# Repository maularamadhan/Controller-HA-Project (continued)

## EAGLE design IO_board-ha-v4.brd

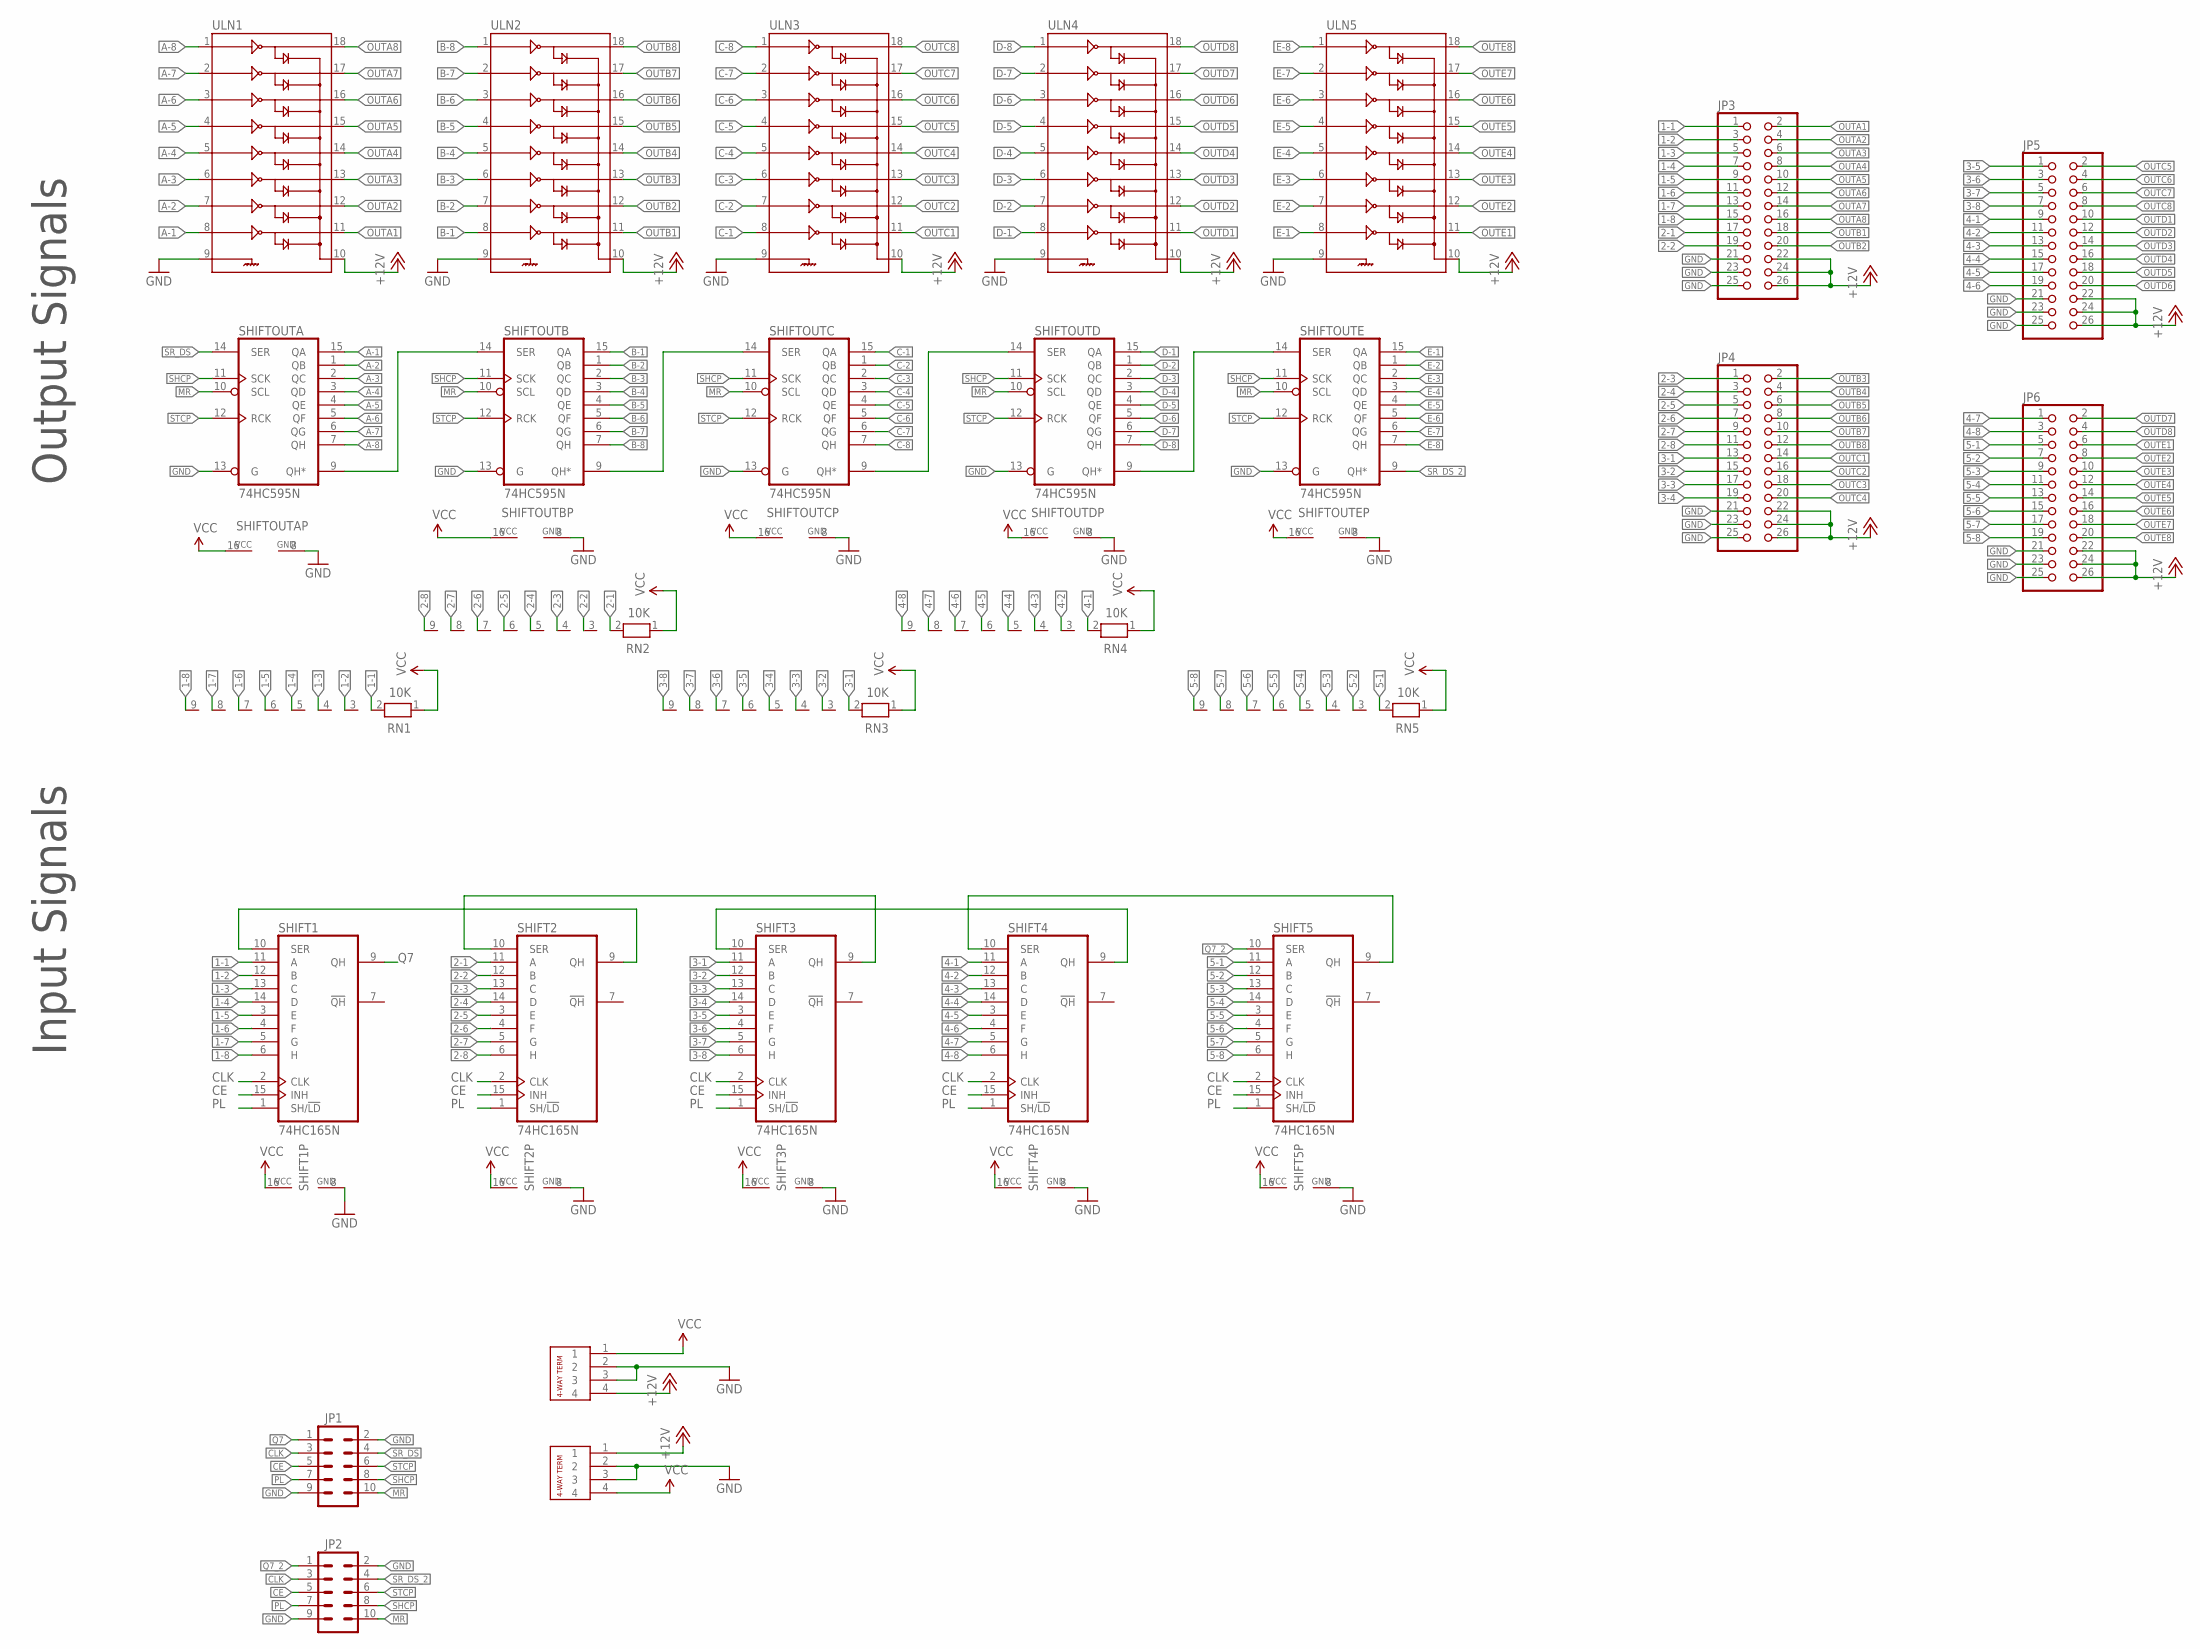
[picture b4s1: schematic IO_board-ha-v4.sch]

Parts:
J1, J2: 4-PIN-CON-1759017
JP1, JP2: M05X2SHD; 2X5-SHROUDED
JP3, JP4, JP5, JP6: PINHD-2X13; 2X13
RN1, RN2, RN3, RN4, RN5: 10K; RN-9
SHIFT1, SHIFT2, SHIFT3, SHIFT4, SHIFT5: 74HC165N; DIL16
SHIFTOUTA: 74HC595N; DIL16
SHIFTOUTB: 74HC595N; DIL16
SHIFTOUTC: 74HC595N; DIL16
SHIFTOUTD: 74HC595N; DIL16
SHIFTOUTE: 74HC595N; DIL16
ULN1, ULN2, ULN3, ULN4, ULN5: ULN2803DIP; DIL18

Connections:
1-1: JP3.1, RN1.2, SHIFT1.11 (A)
1-2: JP3.3, RN1.3, SHIFT1.12 (B)
1-3: JP3.5, RN1.4, SHIFT1.13 (C)
1-4: JP3.7, RN1.5, SHIFT1.14 (D)
1-5: JP3.9, RN1.6, SHIFT1.3 (E)
1-6: JP3.11, RN1.7, SHIFT1.4 (F)
1-7: JP3.13, RN1.8, SHIFT1.5 (G)
1-8: JP3.15, RN1.9, SHIFT1.6 (H)
2-1: JP3.17, RN2.2, SHIFT2.11 (A)
2-2: JP3.19, RN2.3, SHIFT2.12 (B)
2-3: JP4.1, RN2.4, SHIFT2.13 (C)
2-4: JP4.3, RN2.5, SHIFT2.14 (D)
2-5: JP4.5, RN2.6, SHIFT2.3 (E)
2-6: JP4.7, RN2.7, SHIFT2.4 (F)
2-7: JP4.9, RN2.8, SHIFT2.5 (G)
2-8: JP4.11, RN2.9, SHIFT2.6 (H)
3-1: JP4.13, RN3.2, SHIFT3.11 (A)
3-2: JP4.15, RN3.3, SHIFT3.12 (B)
3-3: JP4.17, RN3.4, SHIFT3.13 (C)
3-4: JP4.19, RN3.5, SHIFT3.14 (D)
3-5: JP5.1, RN3.6, SHIFT3.3 (E)
3-6: JP5.3, RN3.7, SHIFT3.4 (F)
3-7: JP5.5, RN3.8, SHIFT3.5 (G)
3-8: JP5.7, RN3.9, SHIFT3.6 (H)
4-1: JP5.9, RN4.2, SHIFT4.11 (A)
4-2: JP5.11, RN4.3, SHIFT4.12 (B)
4-3: JP5.13, RN4.4, SHIFT4.13 (C)
4-4: JP5.15, RN4.5, SHIFT4.14 (D)
4-5: JP5.17, RN4.6, SHIFT4.3 (E)
4-6: JP5.19, RN4.7, SHIFT4.4 (F)
4-7: JP6.1, RN4.8, SHIFT4.5 (G)
4-8: JP6.3, RN4.9, SHIFT4.6 (H)
5-1: JP6.5, RN5.2, SHIFT5.11 (A)
5-2: JP6.7, RN5.3, SHIFT5.12 (B)
5-3: JP6.9, RN5.4, SHIFT5.13 (C)
5-4: JP6.11, RN5.5, SHIFT5.14 (D)
5-5: JP6.13, RN5.6, SHIFT5.3 (E)
5-6: JP6.15, RN5.7, SHIFT5.4 (F)
5-7: JP6.17, RN5.8, SHIFT5.5 (G)
5-8: JP6.19, RN5.9, SHIFT5.6 (H)
+12V: J1.4, J2.1, JP3.22, JP3.24, JP3.26, JP4.22, JP4.24, JP4.26, JP5.22, JP5.24, JP5.26, JP6.22, JP6.24, JP6.26, ULN1.10, ULN2.10, ULN3.10, ULN4.10, ULN5.10
A-1: SHIFTOUTA.15 (QA), ULN1.8
A-2: SHIFTOUTA.1 (QB), ULN1.7
A-3: SHIFTOUTA.2 (QC), ULN1.6
A-4: SHIFTOUTA.3 (QD), ULN1.5
A-5: SHIFTOUTA.4 (QE), ULN1.4
A-6: SHIFTOUTA.5 (QF), ULN1.3
A-7: SHIFTOUTA.6 (QG), ULN1.2
A-8: SHIFTOUTA.7 (QH), ULN1.1
B-1: SHIFTOUTB.15 (QA), ULN2.8
B-2: SHIFTOUTB.1 (QB), ULN2.7
B-3: SHIFTOUTB.2 (QC), ULN2.6
B-4: SHIFTOUTB.3 (QD), ULN2.5
B-5: SHIFTOUTB.4 (QE), ULN2.4
B-6: SHIFTOUTB.5 (QF), ULN2.3
B-7: SHIFTOUTB.6 (QG), ULN2.2
B-8: SHIFTOUTB.7 (QH), ULN2.1
C-1: SHIFTOUTC.15 (QA), ULN3.8
C-2: SHIFTOUTC.1 (QB), ULN3.7
C-3: SHIFTOUTC.2 (QC), ULN3.6
C-4: SHIFTOUTC.3 (QD), ULN3.5
C-5: SHIFTOUTC.4 (QE), ULN3.4
C-6: SHIFTOUTC.5 (QF), ULN3.3
C-7: SHIFTOUTC.6 (QG), ULN3.2
C-8: SHIFTOUTC.7 (QH), ULN3.1
CE: JP1.5, JP2.5, SHIFT1.15 (INH), SHIFT2.15 (INH), SHIFT3.15 (INH), SHIFT4.15 (INH), SHIFT5.15 (INH)
CLK: JP1.3, JP2.3, SHIFT1.2 (CLK), SHIFT2.2 (CLK), SHIFT3.2 (CLK), SHIFT4.2 (CLK), SHIFT5.2 (CLK)
D-1: SHIFTOUTD.15 (QA), ULN4.8
D-2: SHIFTOUTD.1 (QB), ULN4.7
D-3: SHIFTOUTD.2 (QC), ULN4.6
D-4: SHIFTOUTD.3 (QD), ULN4.5
D-5: SHIFTOUTD.4 (QE), ULN4.4
D-6: SHIFTOUTD.5 (QF), ULN4.3
D-7: SHIFTOUTD.6 (QG), ULN4.2
D-8: SHIFTOUTD.7 (QH), ULN4.1
E-1: SHIFTOUTE.15 (QA), ULN5.8
E-2: SHIFTOUTE.1 (QB), ULN5.7
E-3: SHIFTOUTE.2 (QC), ULN5.6
E-4: SHIFTOUTE.3 (QD), ULN5.5
E-5: SHIFTOUTE.4 (QE), ULN5.4
E-6: SHIFTOUTE.5 (QF), ULN5.3
E-7: SHIFTOUTE.6 (QG), ULN5.2
E-8: SHIFTOUTE.7 (QH), ULN5.1
GND: J1.2, J1.3, J2.2, J2.3, JP1.2, JP1.9, JP2.2, JP2.9, JP3.21, JP3.23, JP3.25, JP4.21, JP4.23, JP4.25, JP5.21, JP5.23, JP5.25, JP6.21, JP6.23, JP6.25, SHIFT1.8 (GND), SHIFT2.8 (GND), SHIFT3.8 (GND), SHIFT4.8 (GND), SHIFT5.8 (GND), SHIFTOUTA.8 (GND), SHIFTOUTA.13 (G), SHIFTOUTB.8 (GND), SHIFTOUTB.13 (G), SHIFTOUTC.8 (GND), SHIFTOUTC.13 (G), SHIFTOUTD.8 (GND), SHIFTOUTD.13 (G), SHIFTOUTE.8 (GND), SHIFTOUTE.13 (G), ULN1.9, ULN2.9, ULN3.9, ULN4.9, ULN5.9
MR: JP1.10, JP2.10, SHIFTOUTA.10 (SCL), SHIFTOUTB.10 (SCL), SHIFTOUTC.10 (SCL), SHIFTOUTD.10 (SCL), SHIFTOUTE.10 (SCL)
unnamed: SHIFT2.10 (SER), SHIFT3.9 (QH)
unnamed: SHIFT3.10 (SER), SHIFT4.9 (QH)
unnamed: SHIFT4.10 (SER), SHIFT5.9 (QH)
unnamed: SHIFTOUTA.9 (QH*), SHIFTOUTB.14 (SER)
unnamed: SHIFTOUTC.9 (QH*), SHIFTOUTD.14 (SER)
unnamed: SHIFTOUTB.9 (QH*), SHIFTOUTC.14 (SER)
unnamed: SHIFTOUTD.9 (QH*), SHIFTOUTE.14 (SER)
unnamed: SHIFT1.10 (SER), SHIFT2.9 (QH)
OUTA1: JP3.2, ULN1.11
OUTA2: JP3.4, ULN1.12
OUTA3: JP3.6, ULN1.13
OUTA4: JP3.8, ULN1.14
OUTA5: JP3.10, ULN1.15
OUTA6: JP3.12, ULN1.16
OUTA7: JP3.14, ULN1.17
OUTA8: JP3.16, ULN1.18
OUTB1: JP3.18, ULN2.11
OUTB2: JP3.20, ULN2.12
OUTB3: JP4.2, ULN2.13
OUTB4: JP4.4, ULN2.14
OUTB5: JP4.6, ULN2.15
OUTB6: JP4.8, ULN2.16
OUTB7: JP4.10, ULN2.17
OUTB8: JP4.12, ULN2.18
OUTC1: JP4.14, ULN3.11
OUTC2: JP4.16, ULN3.12
OUTC3: JP4.18, ULN3.13
OUTC4: JP4.20, ULN3.14
OUTC5: JP5.2, ULN3.15
OUTC6: JP5.4, ULN3.16
OUTC7: JP5.6, ULN3.17
OUTC8: JP5.8, ULN3.18
OUTD1: JP5.10, ULN4.11
OUTD2: JP5.12, ULN4.12
OUTD3: JP5.14, ULN4.13
OUTD4: JP5.16, ULN4.14
OUTD5: JP5.18, ULN4.15
OUTD6: JP5.20, ULN4.16
OUTD7: JP6.2, ULN4.17
OUTD8: JP6.4, ULN4.18
OUTE1: JP6.6, ULN5.11
OUTE2: JP6.8, ULN5.12
OUTE3: JP6.10, ULN5.13
OUTE4: JP6.12, ULN5.14
OUTE5: JP6.14, ULN5.15
OUTE6: JP6.16, ULN5.16
OUTE7: JP6.18, ULN5.17
OUTE8: JP6.20, ULN5.18
PL: JP1.7, JP2.7, SHIFT1.1 (SH/!LD), SHIFT2.1 (SH/!LD), SHIFT3.1 (SH/!LD), SHIFT4.1 (SH/!LD), SHIFT5.1 (SH/!LD)
Q7: JP1.1, SHIFT1.9 (QH)
Q7_2: JP2.1, SHIFT5.10 (SER)
SHCP: JP1.8, JP2.8, SHIFTOUTA.11 (SCK), SHIFTOUTB.11 (SCK), SHIFTOUTC.11 (SCK), SHIFTOUTD.11 (SCK), SHIFTOUTE.11 (SCK)
SR_DS: JP1.4, SHIFTOUTA.14 (SER)
SR_DS_2: JP2.4, SHIFTOUTE.9 (QH*)
STCP: JP1.6, JP2.6, SHIFTOUTA.12 (RCK), SHIFTOUTB.12 (RCK), SHIFTOUTC.12 (RCK), SHIFTOUTD.12 (RCK), SHIFTOUTE.12 (RCK)
VCC: J1.1, J2.4, RN1.1, RN2.1, RN3.1, RN4.1, RN5.1, SHIFT1.16 (VCC), SHIFT2.16 (VCC), SHIFT3.16 (VCC), SHIFT4.16 (VCC), SHIFT5.16 (VCC), SHIFTOUTA.16 (VCC), SHIFTOUTB.16 (VCC), SHIFTOUTC.16 (VCC), SHIFTOUTD.16 (VCC), SHIFTOUTE.16 (VCC)

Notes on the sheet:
Input Signals
Output Signals

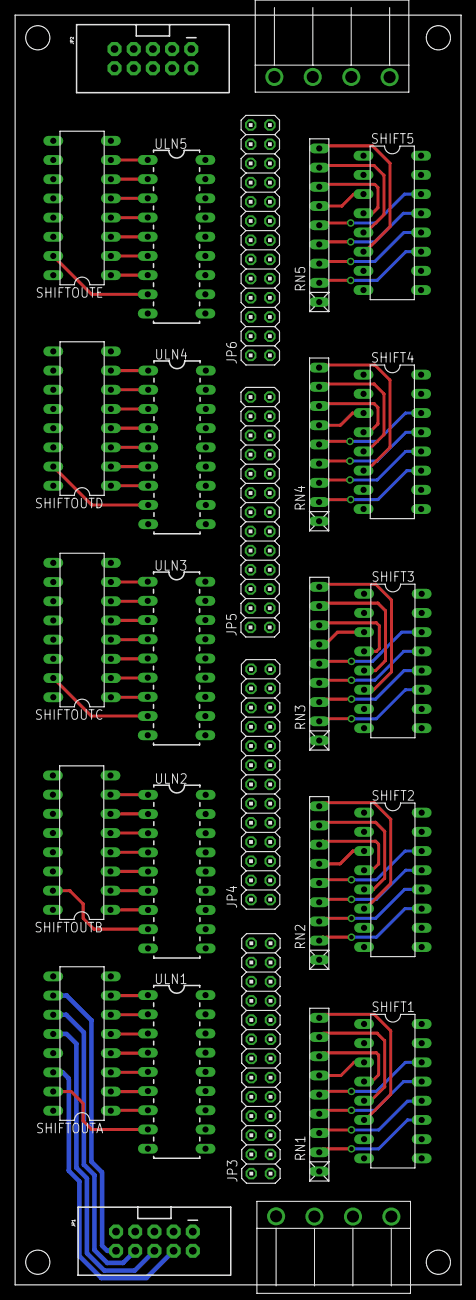
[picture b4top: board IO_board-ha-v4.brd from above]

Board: 2 copper layers, 59.0 x 168.0 mm, 28 parts (0 on the bottom side), 141 nets.

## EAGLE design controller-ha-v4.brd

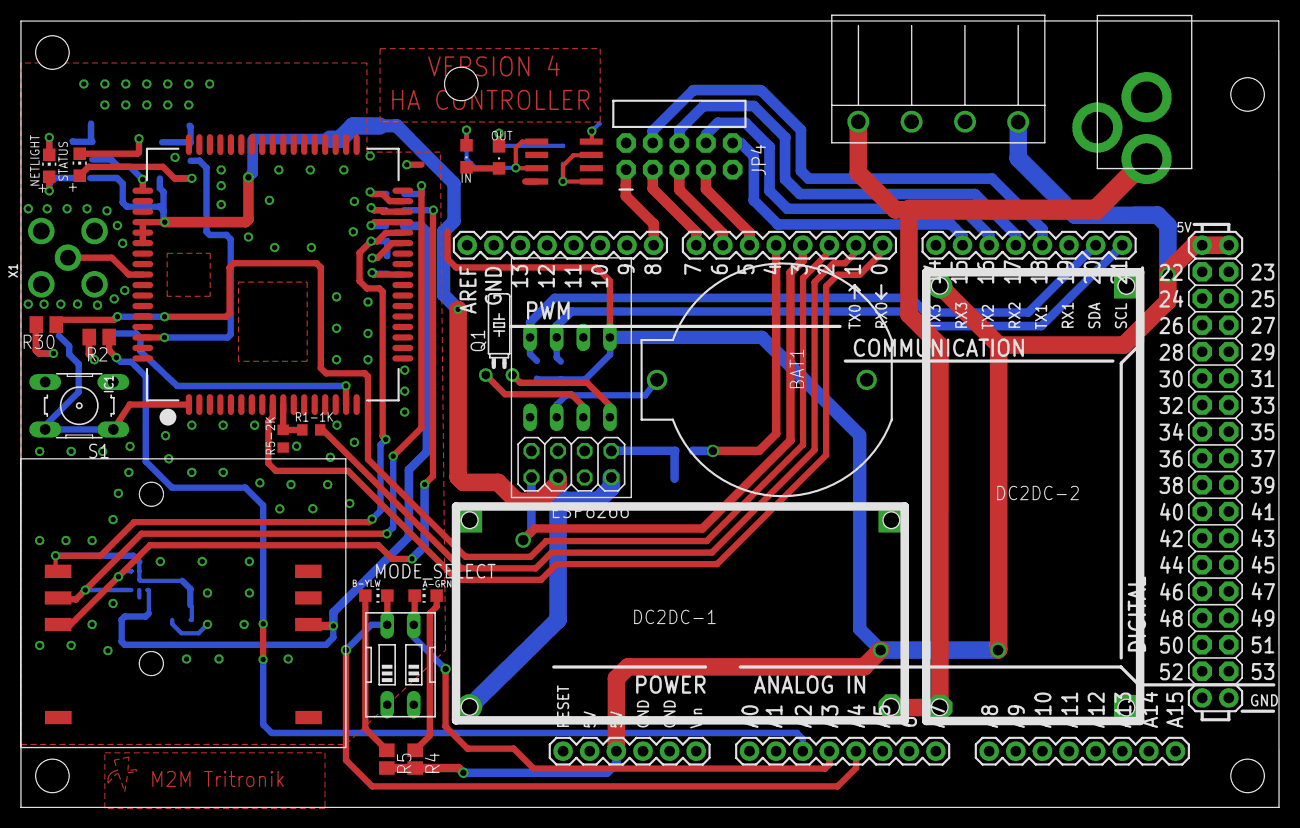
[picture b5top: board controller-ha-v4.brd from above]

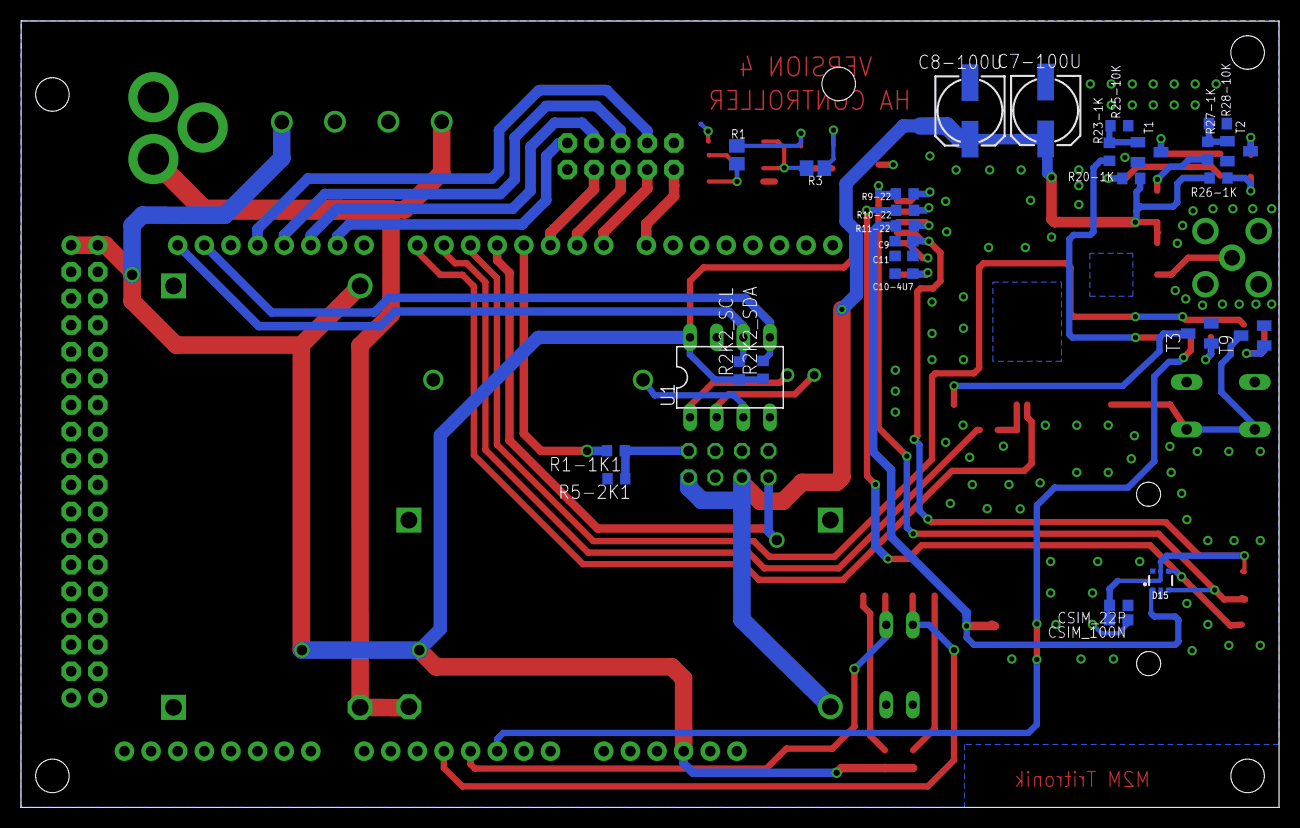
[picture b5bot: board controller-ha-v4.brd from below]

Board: 2 copper layers, 120.0 x 75.0 mm, 55 parts (28 on the bottom side), 54 nets.

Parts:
4-WAY_L-TERMINAL: 4-PIN-CON-1759017
A-GRN: green; CHIP-LED0805
ARDUINO_FOOTPRINT: ARDUINO-MEGAFULL; ARDUINO_MEGA
B-YLW: yellow; CHIP-LED0805
BAT1: BATTCOM_20MM_PTH
C7-100U, C8-100U: 100uF; 153CLV-0605
C9: 100nF; C0603
C10-4U7: 4.7nF; C0603
C11: 22pF; C0603
CSIM_22P: 22pF; C0603K
CSIM_100N: 100nF; C0603K
D15: SOT363
DC2DC-1, DC2DC-2: DCDCMODULE
DC_JACKTHM: 2.1MMJACKTHM; PJ-102A
ESP8266: ESP8266
IC1: SIM900_SMT
IC2: LM358MX; SO08
IN: green; CHIPLED_0805
JP4: 2X5-RA
MODE_SELECT: EDG-02
NETLIGHT: green; CHIP-LED0805
OUT: green; CHIPLED_0805
Q1: TC26H
R1, R3: 220; R0805
R1-1K, R1-1K1, R20-1K, R23-1K, R26-1K, R27-1K: 1K; R0603
R2, R30: 120; M0805
R2K2_SCL, R2K2_SDA: 2.2K; R0603
R4, R5: 1K; R0805
R5-2K, R5-2K1: 2K; R0603
R9-22, R10-22, R11-22: 22; R0603
R25-10K, R28-10K: 10K; R0603
S1: B3F-10XX
SIM_HOLDER: SIM_HOLDER_PUSH
STATUS: yellow; CHIP-LED0805
T1, T2, T3, T9: SOT23-BEC
U1: DS1307; DIL08
X1: SMA90_DIP

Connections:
+3V3: C7-100U.+, C8-100U.+, DC2DC-1.VOUT, ESP8266.CHPD, ESP8266.VCC, IC1.P$55, IC1.P$56, IC1.P$57, R20-1K.2, R26-1K.2
+12V: 4-WAY_L-TERMINAL.4, DC2DC-1.VIN, DC2DC-2.VIN, DC_JACKTHM.TIP
CE: ARDUINO_FOOTPRINT.6, JP4.5
CLK: ARDUINO_FOOTPRINT.7, JP4.3
CTRL_SIMRESET: ARDUINO_FOOTPRINT.A2, R2.1
ESP_RX: ESP8266.RXD, R1-1K1.1, R5-2K1.2
ESP_RXX: ARDUINO_FOOTPRINT.4, R1-1K1.2
ESP_TX: ARDUINO_FOOTPRINT.3, ESP8266.TXD
GND: 4-WAY_L-TERMINAL.2, 4-WAY_L-TERMINAL.3, ARDUINO_FOOTPRINT.GND@0, ARDUINO_FOOTPRINT.GND@1, ARDUINO_FOOTPRINT.GND@2, ARDUINO_FOOTPRINT.GND@3, ARDUINO_FOOTPRINT.GND@4, BAT1.2, C7-100U.-, C8-100U.-, C9.2, C10-4U7.2, C11.2, CSIM_22P.1, CSIM_100N.1, D15.2, DC2DC-1.GND#0, DC2DC-1.GND#1, DC2DC-2.GND#0, DC2DC-2.GND#1, DC_JACKTHM.RING, DC_JACKTHM.RING_SW, ESP8266.GND, IC1.P$17, IC1.P$18, IC1.P$29, IC1.P$39, IC1.P$45, IC1.P$46, IC1.P$53, IC1.P$54, IC1.P$58, IC1.P$59, IC1.P$61, IC1.P$62, IC1.P$63, IC1.P$64, IC1.P$65, IC2.4, IN.C, JP4.2, JP4.9, MODE_SELECT.1, MODE_SELECT.2, OUT.C, R5-2K.1, R5-2K1.1, R25-10K.2, R28-10K.2, S1.3, S1.4, SIM_HOLDER.GND, T1.E, T2.E, T3.E, T9.E, U1.4, X1.GND1, X1.GND2, X1.GND3, X1.GND4
unnamed: ARDUINO_FOOTPRINT.1, R1-1K.2
unnamed: IC1.P$31, R11-22.1
unnamed: IC1.P$32, R10-22.1
unnamed: IC1.P$33, R9-22.1
unnamed: C10-4U7.1, IC1.P$26
unnamed: IC1.P$60, X1.ANTENNA
unnamed: R20-1K.1, STATUS.A
unnamed: STATUS.C, T1.C
unnamed: R23-1K.1, R25-10K.1, T1.B
unnamed: NETLIGHT.A, R26-1K.1
unnamed: NETLIGHT.C, T2.C
unnamed: R27-1K.1, R28-10K.1, T2.B
unnamed: R30.2, T9.B
unnamed: R2.2, T3.B
unnamed: Q1.1, U1.2
unnamed: Q1.2, U1.1
unnamed: IC2.1, IC2.3, R1.1
unnamed: BAT1.1, U1.3
unnamed: IC2.5, IC2.7, R3.1
unnamed: OUT.A, R1.2
unnamed: IN.A, R3.2
unnamed: A-GRN.A, R4.1
unnamed: B-YLW.A, R5.1
PL: ARDUINO_FOOTPRINT.5, JP4.7
PWRKEY: ARDUINO_FOOTPRINT.2, R30.1
Q7: ARDUINO_FOOTPRINT.8, IC2.2, JP4.1
SCL: ARDUINO_FOOTPRINT.21, R2K2_SCL.2, U1.6
SDA: ARDUINO_FOOTPRINT.20, R2K2_SDA.2, U1.5
SHCP: ARDUINO_FOOTPRINT.16, JP4.8
SIM_NETLIGHT: IC1.P$52, R27-1K.2
SIM_PWRKEY: IC1.P$1, S1.1, S1.2, T9.C
SIM_RESET: IC1.P$16, T3.C
SIM_RX: IC1.P$10, R1-1K.1, R5-2K.2
SIM_STATUS: IC1.P$66, R23-1K.2
SIM_TX: ARDUINO_FOOTPRINT.0, IC1.P$9
SR_DS: ARDUINO_FOOTPRINT.18, IC2.6, JP4.4
SR_RST: ARDUINO_FOOTPRINT.15, JP4.10
STATE_A: A-GRN.C, ARDUINO_FOOTPRINT.A3, MODE_SELECT.3
STATE_B: ARDUINO_FOOTPRINT.A4, B-YLW.C, MODE_SELECT.4
STCP: ARDUINO_FOOTPRINT.17, JP4.6
USIM_CLK: D15.4, R10-22.2, SIM_HOLDER.CLK
USIM_DATA: D15.1, R11-22.2, SIM_HOLDER.I/O
USIM_RESET: D15.3, R9-22.2, SIM_HOLDER.RST
USIM_VCC: C9.1, C11.1, CSIM_22P.2, CSIM_100N.2, D15.5, IC1.P$30, SIM_HOLDER.VCC
VCC: 4-WAY_L-TERMINAL.1, ARDUINO_FOOTPRINT.5V@0, ARDUINO_FOOTPRINT.5V@1, ARDUINO_FOOTPRINT.5V@2, DC2DC-2.VOUT, IC2.8, R2K2_SCL.1, R2K2_SDA.1, R4.2, R5.2, U1.8

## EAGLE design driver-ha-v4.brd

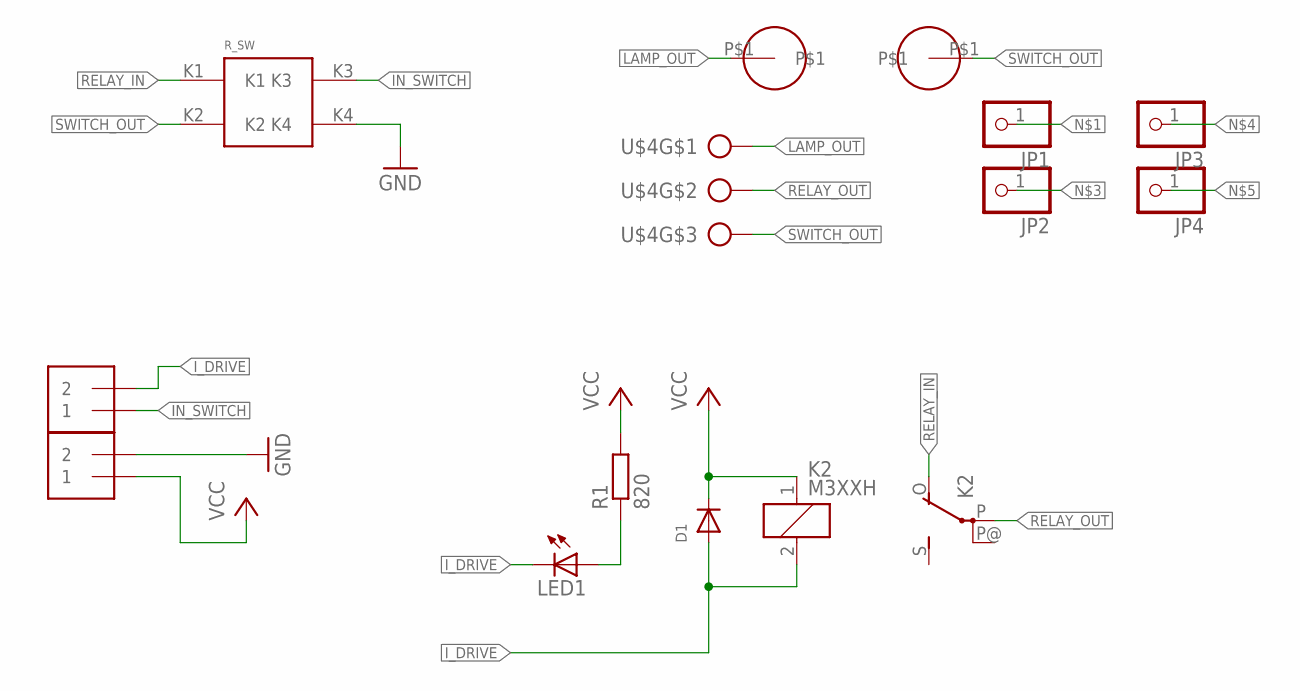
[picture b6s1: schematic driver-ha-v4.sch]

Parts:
D1: DIODESMA; SMADIODE
J1, J2: 1X2-3.5MM
JP1, JP2, JP3, JP4: PINHD-1X1; 1X01
K2: M3XXH
LED1: LEDCHIPLED_0805; CHIPLED_0805
PAD1: ROOM_SWITCH
R1: 820; R0805
U$1, U$3: CONN-CABLE
U$4: AK3003

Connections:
GND: J2.2, PAD1.K4
IN_SWITCH: J1.1, PAD1.K3
I_DRIVE: D1.A, J1.2, K2.2, LED1.C
LAMP_OUT: U$1.P$1, U$4.1
unnamed: LED1.A, R1.1
RELAY_IN: K2.O, PAD1.K1
RELAY_OUT: K2.P, U$4.2
SWITCH_OUT: PAD1.K2, U$3.P$1, U$4.3
VCC: D1.C, J2.1, K2.1, R1.2

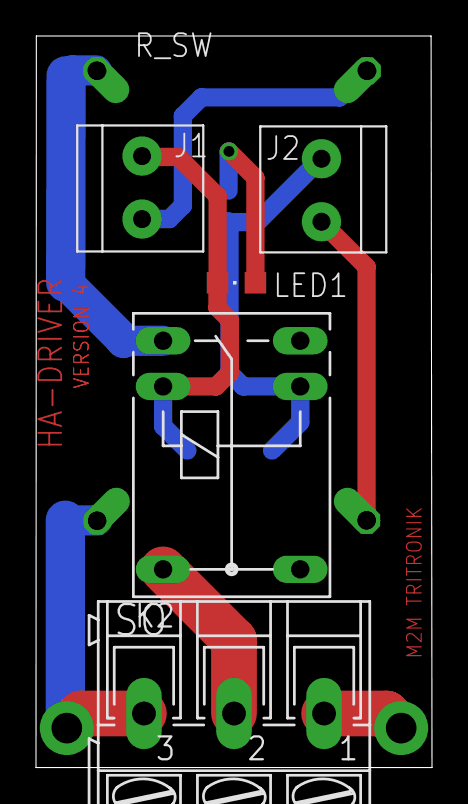
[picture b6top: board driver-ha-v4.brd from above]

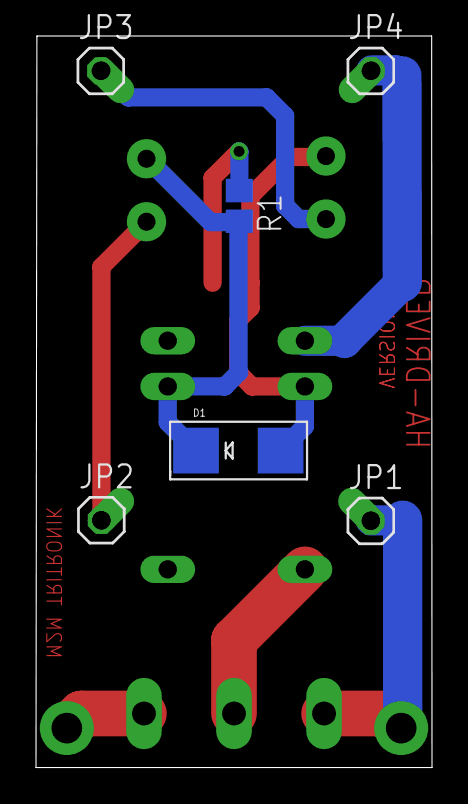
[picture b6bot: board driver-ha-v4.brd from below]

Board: 2 copper layers, 22.0 x 40.6 mm, 14 parts (6 on the bottom side), 9 nets.

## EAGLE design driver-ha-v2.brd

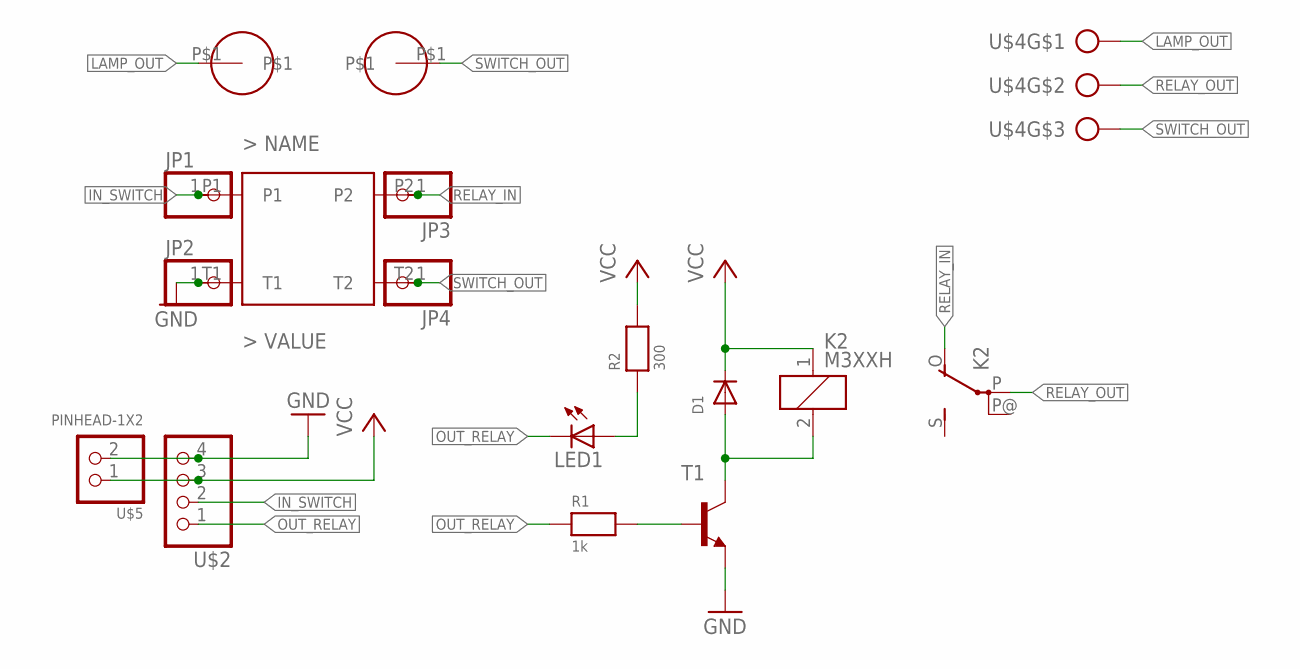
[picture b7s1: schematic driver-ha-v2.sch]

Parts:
D1: DIODESMA; SMADIODE
JP1, JP2, JP3, JP4: PINHD-1X1; 1X01
K2: M3XXH
LED1: LEDCHIPLED_0805; CHIPLED_0805
R1: 1k; 0603
R2: 300; 0603
ROOM_SWITCH: DPST-SWITCH-1221; TOGGLE-SW-E1221
T1: MMBT2222ALT1-NPN-SOT23-BEC; SOT23-BEC
U$1, U$3: CONN-CABLE
U$2: HEADER-1X4; 1X04_OVAL
U$4: AK3003
U$5: PINHEAD-1X2; PIHEAD-1X2

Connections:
GND: JP2.1, ROOM_SWITCH.T1, T1.E, U$2.4, U$5.2
IN_SWITCH: JP1.1, ROOM_SWITCH.P1, U$2.2
LAMP_OUT: U$1.P$1, U$4.1
unnamed: R1.2, T1.B
unnamed: LED1.A, R2.1
unnamed: D1.A, K2.2, T1.C
OUT_RELAY: LED1.C, R1.1, U$2.1
RELAY_IN: JP3.1, K2.O, ROOM_SWITCH.P2
RELAY_OUT: K2.P, U$4.2
SWITCH_OUT: JP4.1, ROOM_SWITCH.T2, U$3.P$1, U$4.3
VCC: D1.C, K2.1, R2.2, U$2.3, U$5.1

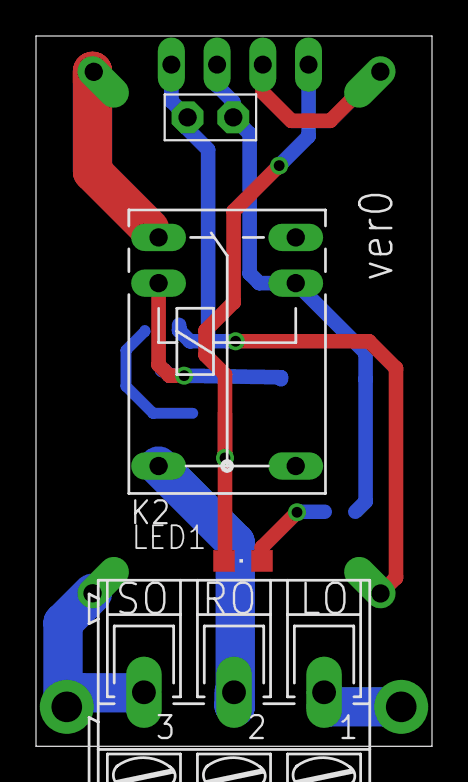
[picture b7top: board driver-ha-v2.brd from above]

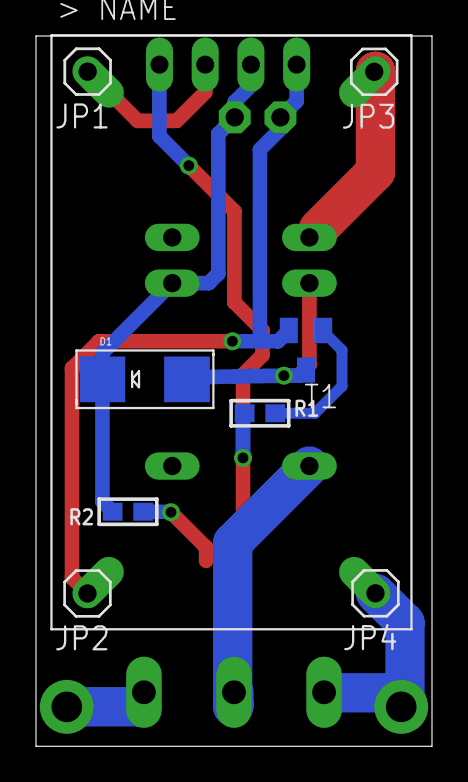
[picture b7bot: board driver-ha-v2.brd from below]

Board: 2 copper layers, 22.0 x 39.5 mm, 16 parts (9 on the bottom side), 11 nets.

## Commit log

2015-10-26 :neckbeard: Added .gitattributes & .gitignore files
2015-10-26 Finish routing
    All route has been route. This is the first version of the file.
2015-10-27 Finish routing and Update Arduino footprint
    Check out the .brd and .sch files
2015-10-29 Update to ver2
    Added : Capacitors, DC/DC, DC input jack; Re-routed (fixed
    too-close-through holes) + 9V DC and VCC clearence
2015-11-19 updated to ver3
    Version 3 is separating the Main Controller and the I/O Module
2015-12-16 Submit all new design
    Adding version 3-4 for driver & controller; Adding version 1-2 IO Module
2015-12-18 change in controller design
    Change component position & adding hole to controller design
2016-01-21 Revising Controller & IO Module
    Some module (SIM900 & RTC) are not working, IO Module suddenly shorted
2016-05-18 Uptade all fixed design
    This is whole new update for all device version
2016-06-02 Tiding up and add a new ha-driver
    revised the ha-driver to 1-layer PCB
2016-06-03 Add 5th version of HA-Controller
    This version disable SIM900 and enable Ethernet
2016-06-06 autoroute
    remove gnd plane, add gnd route
2016-08-22 Upgrade to version 5
    With LAN Ethernet ENC28J60; adding relay for restarting 12V modules
    (Driver & IO).
2016-09-20 Update for controller & IO-Modules
    adding LED to IO. adding LAN to controller
